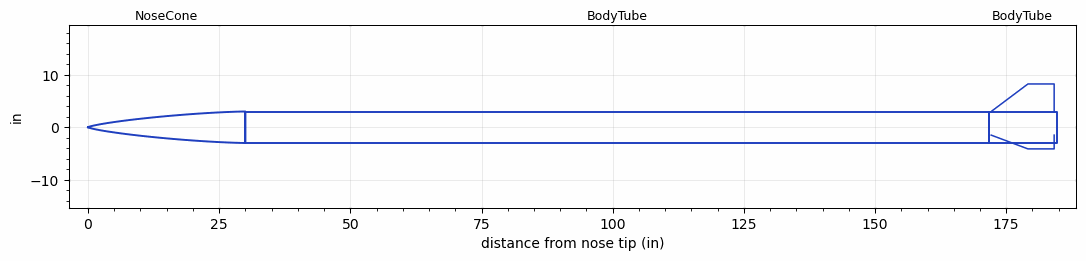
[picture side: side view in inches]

<RASAeroDocument>
 <FileVersion>2</FileVersion>
 <RocketDesign>
  <NoseCone>
   <Length>30</Length>
   <Diameter>6</Diameter>
   <Shape>Von Karman Ogive</Shape>
   <BluntRadius>0.086</BluntRadius>
   <Location>0</Location>
  </NoseCone>
  <BodyTube>
   <Length>141.639</Length>
   <Diameter>6</Diameter>
   <Location>30</Location>
  </BodyTube>
  <BodyTube>
   <Length>13</Length>
   <Diameter>6</Diameter>
   <Location>171.639</Location>
   <Fin>
    <Count>3</Count>
    <Chord>12</Chord>
    <Span>5.25</Span>
    <SweepDistance>7</SweepDistance>
    <TipChord>5</TipChord>
    <Thickness>0.118</Thickness>
    <Location>12.5</Location>
    <AirfoilSection>Rounded</AirfoilSection>
   </Fin>
  </BodyTube>
  <Surface>Smooth (Zero Roughness)</Surface>
  <ModifiedBarrowman>False</ModifiedBarrowman>
  <Turbulence>False</Turbulence>
  <UseBooster1>False</UseBooster1>
  <UseBooster2>False</UseBooster2>
 </RocketDesign>
 <LaunchSite>
  <Altitude>0</Altitude>
  <Pressure>0</Pressure>
  <RodAngle>0</RodAngle>
  <RodLength>4</RodLength>
  <Temperature>74</Temperature>
  <WindSpeed>0</WindSpeed>
 </LaunchSite>
 <Recovery>
  <Altitude1>1000</Altitude1>
  <Altitude2>1000</Altitude2>
  <DeviceType1>None</DeviceType1>
  <DeviceType2>None</DeviceType2>
  <Event1>False</Event1>
  <Event2>False</Event2>
  <Size1>1</Size1>
  <Size2>1</Size2>
  <EventType1>None</EventType1>
  <EventType2>None</EventType2>
  <CD1>1.33</CD1>
  <CD2>1.33</CD2>
 </Recovery>
</RASAeroDocument>
